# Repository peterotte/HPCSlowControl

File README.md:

# HPCSlowControl
HPC SlowControl for Arduino

This is an sample implementation for the Sensor Aggregation Unit to read out connected OneWire and I2C sensors. 

Arduino Folder
  * Eagle Files (and converted into PDF)
  * Schematics housing as PDF
  * Bootloader with settings fpr ATMEL Mega 328PB

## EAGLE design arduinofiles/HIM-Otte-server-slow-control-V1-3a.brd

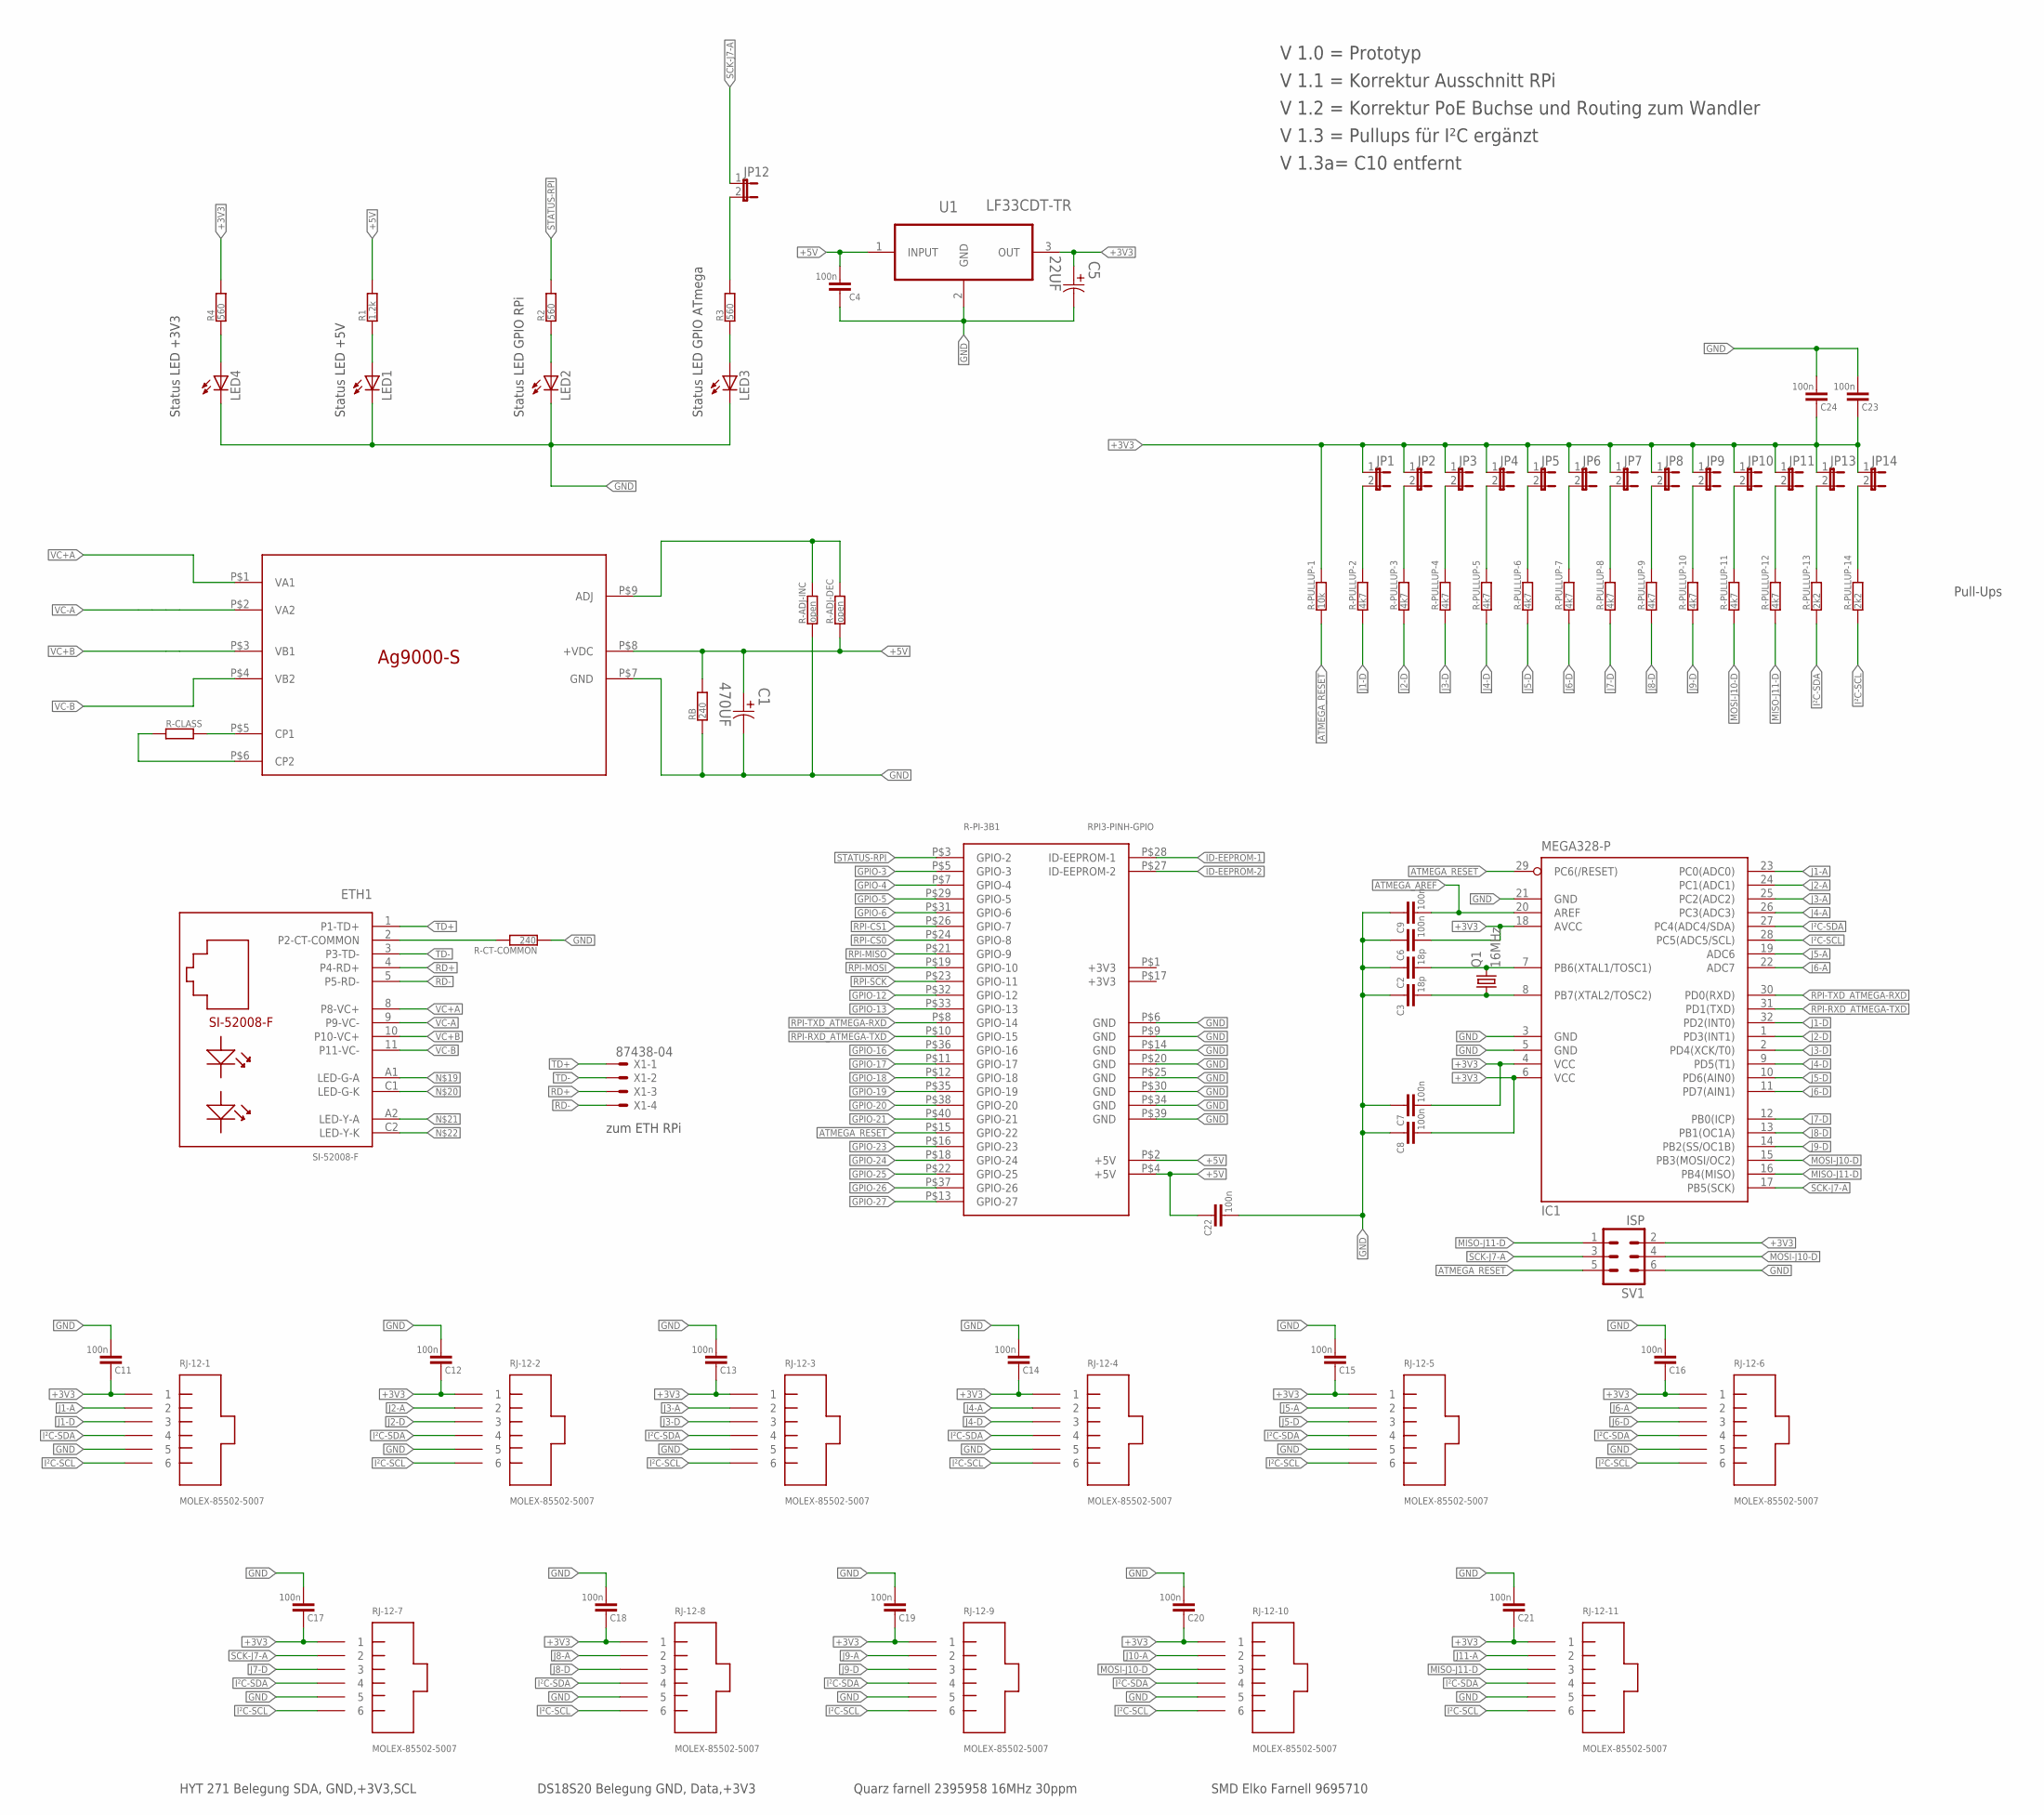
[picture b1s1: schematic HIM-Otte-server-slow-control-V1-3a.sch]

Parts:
C1: 470UF; CAPAE830X1050N
C2, C3: 18p; C0603
C4, C6, C7, C8, C9, C11, C12, C13, C14, C15, C16, C17, C18, C19, C20, C21, C22, C23, C24: 100n; C0603
C5: 22UF; CAPAE530X610N
ETH1: SI-52008-F
IC1: MEGA328-P; TQFP32-08
JP1, JP2, JP3, JP4, JP5, JP6, JP7, JP8, JP9, JP10, JP11, JP12, JP13, JP14: JP1E; JP1
LED1, LED2, LED3, LED4: LEDCHIPLED_0603; CHIPLED_0603
Q1: 16MHz; HC49UP
R1: 1.2k; R0603
R2, R3, R4: 560; R0603
R-ADJ-DEC: open; R0603
R-ADJ-INC: open; R0603
R-CLASS: R-EU_R0603; R0603
R-CT-COMMON: 240; R0603
R-PI-3B1: RPI3-PINH-GPIO
R-PULLUP-1: 10k; R0603
R-PULLUP-2, R-PULLUP-3, R-PULLUP-4, R-PULLUP-5, R-PULLUP-6, R-PULLUP-7, R-PULLUP-8, R-PULLUP-9, R-PULLUP-10, R-PULLUP-11, R-PULLUP-12: 4k7; R0603
R-PULLUP-13, R-PULLUP-14: 2k2; R0603
RB: 240; R0603
RJ-12-1, RJ-12-2, RJ-12-3, RJ-12-4, RJ-12-5, RJ-12-6, RJ-12-7, RJ-12-8, RJ-12-9, RJ-12-10, RJ-12-11: MOLEX-85502-5007
SV1: ISP; ML6
U1: LF33CDT-TR; TO228P972X240-3N
U$1: AG9000-S
X1: 87438-04

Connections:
+3V3: C5.1, C6.2, C7.2, C8.2, C11.1, C12.1, C13.1, C14.1, C15.1, C16.1, C17.1, C18.1, C19.1, C20.1, C21.1, C23.1, C24.1, IC1.4 (VCC), IC1.6 (VCC), IC1.18 (AVCC), JP1.1, JP2.1, JP3.1, JP4.1, JP5.1, JP6.1, JP7.1, JP8.1, JP9.1, JP10.1, JP11.1, JP13.1, JP14.1, R4.2, R-PULLUP-1.2, RJ-12-1.1, RJ-12-2.1, RJ-12-3.1, RJ-12-4.1, RJ-12-5.1, RJ-12-6.1, RJ-12-7.1, RJ-12-8.1, RJ-12-9.1, RJ-12-10.1, RJ-12-11.1, SV1.2, U1.3 (OUT)
+5V: C1.1, C4.2, C22.1, R1.2, R-ADJ-DEC.1, R-PI-3B1.P$2 (+5V), R-PI-3B1.P$4 (+5V), RB.2, U1.1 (INPUT), U$1.P$8 (+VDC)
ATMEGA_AREF: C9.2, IC1.20 (AREF)
ATMEGA_RESET: IC1.29 (PC6(/RESET)), R-PI-3B1.P$15 (GPIO-22), R-PULLUP-1.1, SV1.5
GND: C1.2, C2.1, C3.1, C4.1, C5.2, C6.1, C7.1, C8.1, C9.1, C11.2, C12.2, C13.2, C14.2, C15.2, C16.2, C17.2, C18.2, C19.2, C20.2, C21.2, C22.2, C23.2, C24.2, IC1.3 (GND), IC1.5 (GND), IC1.21 (GND), LED1.C, LED2.C, LED3.C, LED4.C, R-ADJ-INC.1, R-CT-COMMON.1, R-PI-3B1.P$6 (GND), R-PI-3B1.P$9 (GND), R-PI-3B1.P$14 (GND), R-PI-3B1.P$20 (GND), R-PI-3B1.P$25 (GND), R-PI-3B1.P$30 (GND), R-PI-3B1.P$34 (GND), R-PI-3B1.P$39 (GND), RB.1, RJ-12-1.5, RJ-12-2.5, RJ-12-3.5, RJ-12-4.5, RJ-12-5.5, RJ-12-6.5, RJ-12-7.5, RJ-12-8.5, RJ-12-9.5, RJ-12-10.5, RJ-12-11.5, SV1.6, U1.2 (GND), U$1.P$7 (GND)
GPIO-3: R-PI-3B1.P$5 (GPIO-3)
GPIO-4: R-PI-3B1.P$7 (GPIO-4)
GPIO-5: R-PI-3B1.P$29 (GPIO-5)
GPIO-6: R-PI-3B1.P$31 (GPIO-6)
GPIO-12: R-PI-3B1.P$32 (GPIO-12)
GPIO-13: R-PI-3B1.P$33 (GPIO-13)
GPIO-16: R-PI-3B1.P$36 (GPIO-16)
GPIO-17: R-PI-3B1.P$11 (GPIO-17)
GPIO-18: R-PI-3B1.P$12 (GPIO-18)
GPIO-19: R-PI-3B1.P$35 (GPIO-19)
GPIO-20: R-PI-3B1.P$38 (GPIO-20)
GPIO-21: R-PI-3B1.P$40 (GPIO-21)
GPIO-23: R-PI-3B1.P$16 (GPIO-23)
GPIO-24: R-PI-3B1.P$18 (GPIO-24)
GPIO-25: R-PI-3B1.P$22 (GPIO-25)
GPIO-26: R-PI-3B1.P$37 (GPIO-26)
GPIO-27: R-PI-3B1.P$13 (GPIO-27)
ID-EEPROM-1: R-PI-3B1.P$28 (ID-EEPROM-1)
ID-EEPROM-2: R-PI-3B1.P$27 (ID-EEPROM-2)
I²C-SCL: IC1.28 (PC5(ADC5/SCL)), R-PULLUP-14.1, RJ-12-1.6, RJ-12-2.6, RJ-12-3.6, RJ-12-4.6, RJ-12-5.6, RJ-12-6.6, RJ-12-7.6, RJ-12-8.6, RJ-12-9.6, RJ-12-10.6, RJ-12-11.6
I²C-SDA: IC1.27 (PC4(ADC4/SDA)), R-PULLUP-13.1, RJ-12-1.4, RJ-12-2.4, RJ-12-3.4, RJ-12-4.4, RJ-12-5.4, RJ-12-6.4, RJ-12-7.4, RJ-12-8.4, RJ-12-9.4, RJ-12-10.4, RJ-12-11.4
J1-A: IC1.23 (PC0(ADC0)), RJ-12-1.2
J1-D: IC1.32 (PD2(INT0)), R-PULLUP-2.1, RJ-12-1.3
J2-A: IC1.24 (PC1(ADC1)), RJ-12-2.2
J2-D: IC1.1 (PD3(INT1)), R-PULLUP-3.1, RJ-12-2.3
J3-A: IC1.25 (PC2(ADC2)), RJ-12-3.2
J3-D: IC1.2 (PD4(XCK/T0)), R-PULLUP-4.1, RJ-12-3.3
J4-A: IC1.26 (PC3(ADC3)), RJ-12-4.2
J4-D: IC1.9 (PD5(T1)), R-PULLUP-5.1, RJ-12-4.3
J5-A: IC1.19 (ADC6), RJ-12-5.2
J5-D: IC1.10 (PD6(AIN0)), R-PULLUP-6.1, RJ-12-5.3
J6-A: IC1.22 (ADC7), RJ-12-6.2
J6-D: IC1.11 (PD7(AIN1)), R-PULLUP-7.1, RJ-12-6.3
J7-D: IC1.12 (PB0(ICP)), R-PULLUP-8.1, RJ-12-7.3
J8-A: RJ-12-8.2
J8-D: IC1.13 (PB1(OC1A)), R-PULLUP-9.1, RJ-12-8.3
J9-A: RJ-12-9.2
J9-D: IC1.14 (PB2(SS/OC1B)), R-PULLUP-10.1, RJ-12-9.3
J10-A: RJ-12-10.2
J11-A: RJ-12-11.2
MISO-J11-D: IC1.16 (PB4(MISO)), R-PULLUP-12.1, RJ-12-11.3, SV1.1
MOSI-J10-D: IC1.15 (PB3(MOSI/OC2)), R-PULLUP-11.1, RJ-12-10.3, SV1.4
unnamed: JP11.2, R-PULLUP-12.2
unnamed: JP10.2, R-PULLUP-11.2
unnamed: JP9.2, R-PULLUP-10.2
unnamed: JP8.2, R-PULLUP-9.2
unnamed: R-CLASS.2, U$1.P$5 (CP1)
unnamed: R-CLASS.1, U$1.P$6 (CP2)
unnamed: R-ADJ-DEC.2, R-ADJ-INC.2, U$1.P$9 (ADJ)
unnamed: C2.2, IC1.7 (PB6(XTAL1/TOSC1)), Q1.2
unnamed: C3.2, IC1.8 (PB7(XTAL2/TOSC2)), Q1.1
unnamed: JP7.2, R-PULLUP-8.2
unnamed: ETH1.2 (P2-CT-COMMON), R-CT-COMMON.2
unnamed: JP6.2, R-PULLUP-7.2
unnamed: JP5.2, R-PULLUP-6.2
unnamed: JP4.2, R-PULLUP-5.2
unnamed: JP3.2, R-PULLUP-4.2
unnamed: JP2.2, R-PULLUP-3.2
unnamed: JP1.2, R-PULLUP-2.2
unnamed: LED4.A, R4.1
unnamed: JP12.2, R3.2
unnamed: JP13.2, R-PULLUP-13.2
unnamed: JP14.2, R-PULLUP-14.2
unnamed: LED1.A, R1.1
unnamed: LED2.A, R2.1
unnamed: LED3.A, R3.1
RD+: ETH1.4 (P4-RD+), X1.3
RD-: ETH1.5 (P5-RD-), X1.4
RPI-CS0: R-PI-3B1.P$24 (GPIO-8)
RPI-CS1: R-PI-3B1.P$26 (GPIO-7)
RPI-MISO: R-PI-3B1.P$21 (GPIO-9)
RPI-MOSI: R-PI-3B1.P$19 (GPIO-10)
RPI-RXD_ATMEGA-TXD: IC1.31 (PD1(TXD)), R-PI-3B1.P$10 (GPIO-15)
RPI-SCK: R-PI-3B1.P$23 (GPIO-11)
RPI-TXD_ATMEGA-RXD: IC1.30 (PD0(RXD)), R-PI-3B1.P$8 (GPIO-14)
SCK-J7-A: IC1.17 (PB5(SCK)), JP12.1, RJ-12-7.2, SV1.3
STATUS-RPI: R2.2, R-PI-3B1.P$3 (GPIO-2)
TD+: ETH1.1 (P1-TD+), X1.1
TD-: ETH1.3 (P3-TD-), X1.2
VC+A: ETH1.8 (P8-VC+), U$1.P$1 (VA1)
VC+B: ETH1.10 (P10-VC+), U$1.P$3 (VB1)
VC-A: ETH1.9 (P9-VC-), U$1.P$2 (VA2)
VC-B: ETH1.11 (P11-VC-), U$1.P$4 (VB2)

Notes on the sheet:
Status LED +5V
Status LED GPIO RPi
Status LED GPIO ATmega
HYT 271 Belegung SDA, GND,+3V3,SCL
DS18S20 Belegung GND, Data,+3V3
SMD Elko Farnell 9695710
Quarz farnell 2395958 16MHz 30ppm
zum ETH RPi
Pull-Ups
Status LED +3V3
V 1.0 = Prototyp
V 1.1 = Korrektur Ausschnitt RPi
V 1.2 = Korrektur PoE Buchse und Routing zum Wandler
V 1.3 = Pullups für I²C ergänzt
V 1.3a= C10 entfernt

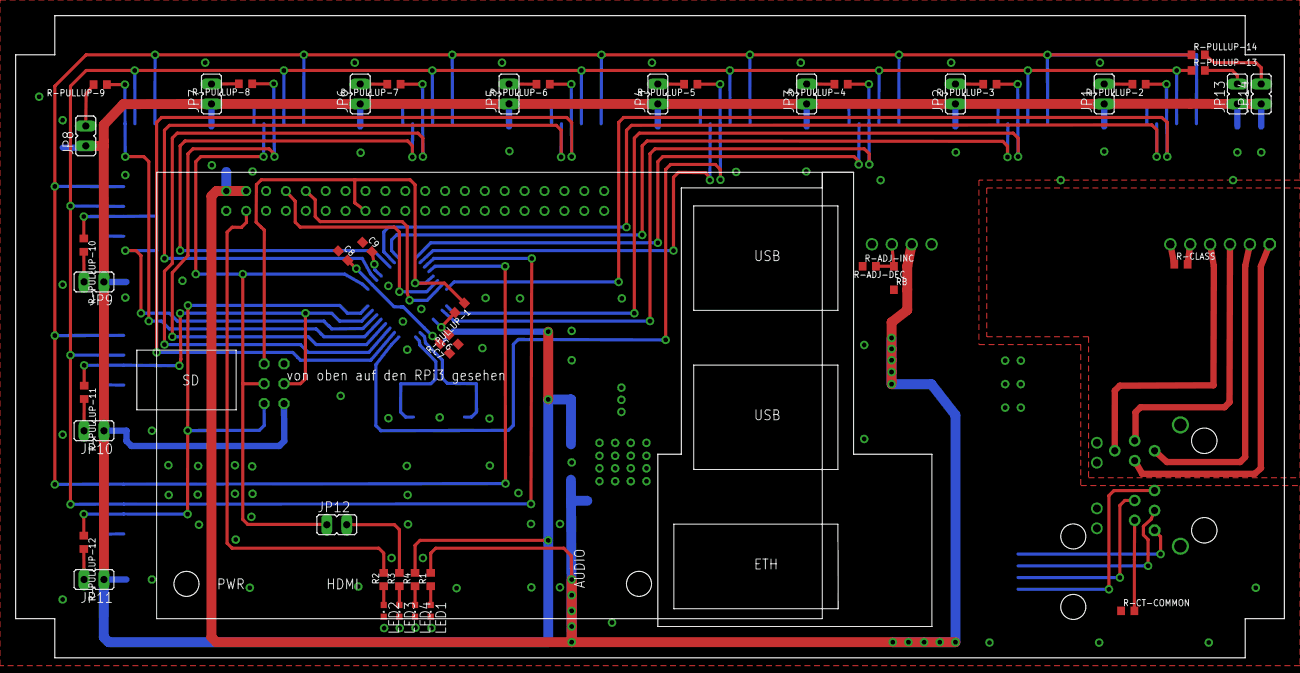
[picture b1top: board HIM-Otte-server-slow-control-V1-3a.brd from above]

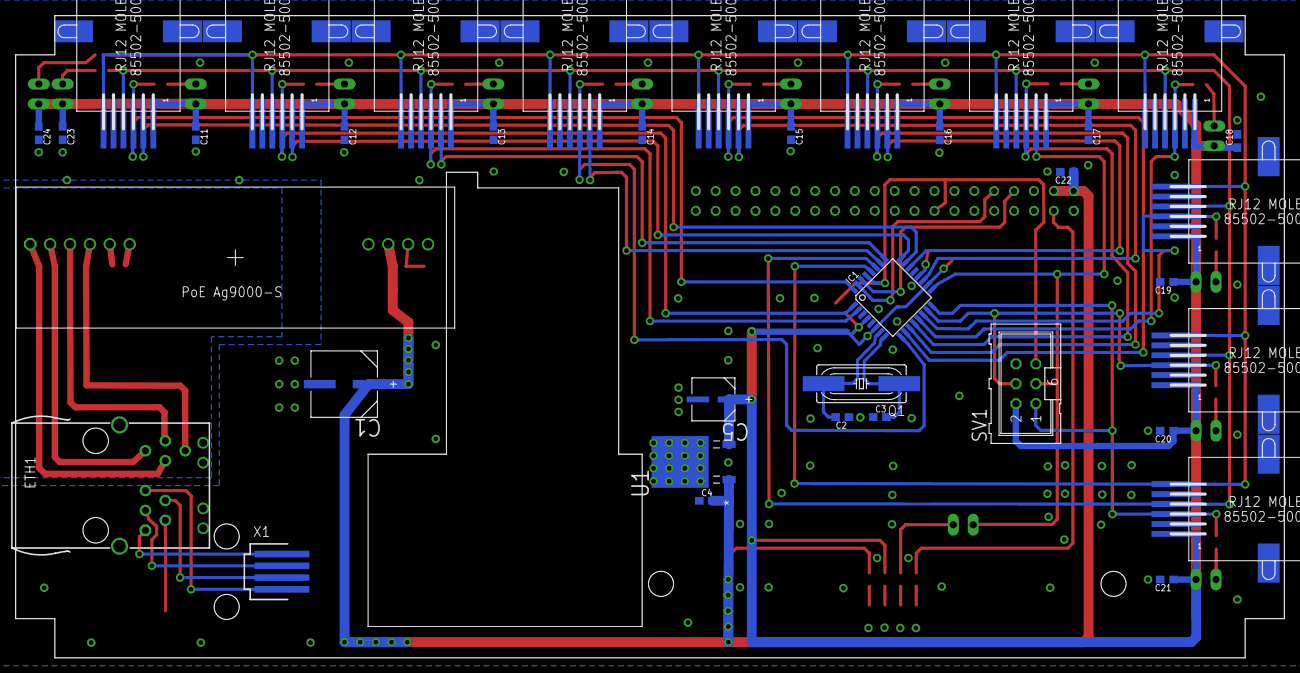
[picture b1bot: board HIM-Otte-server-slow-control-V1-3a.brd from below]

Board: 2 copper layers, 162.0 x 82.0 mm, 83 parts (37 on the bottom side), 60 nets.

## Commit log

2016-06-06 no message
2017-09-26 Arduino files added
    Schematics, derber files, and details for flashing added.
2017-09-28 C10 removed
    All affected files have been updated.
